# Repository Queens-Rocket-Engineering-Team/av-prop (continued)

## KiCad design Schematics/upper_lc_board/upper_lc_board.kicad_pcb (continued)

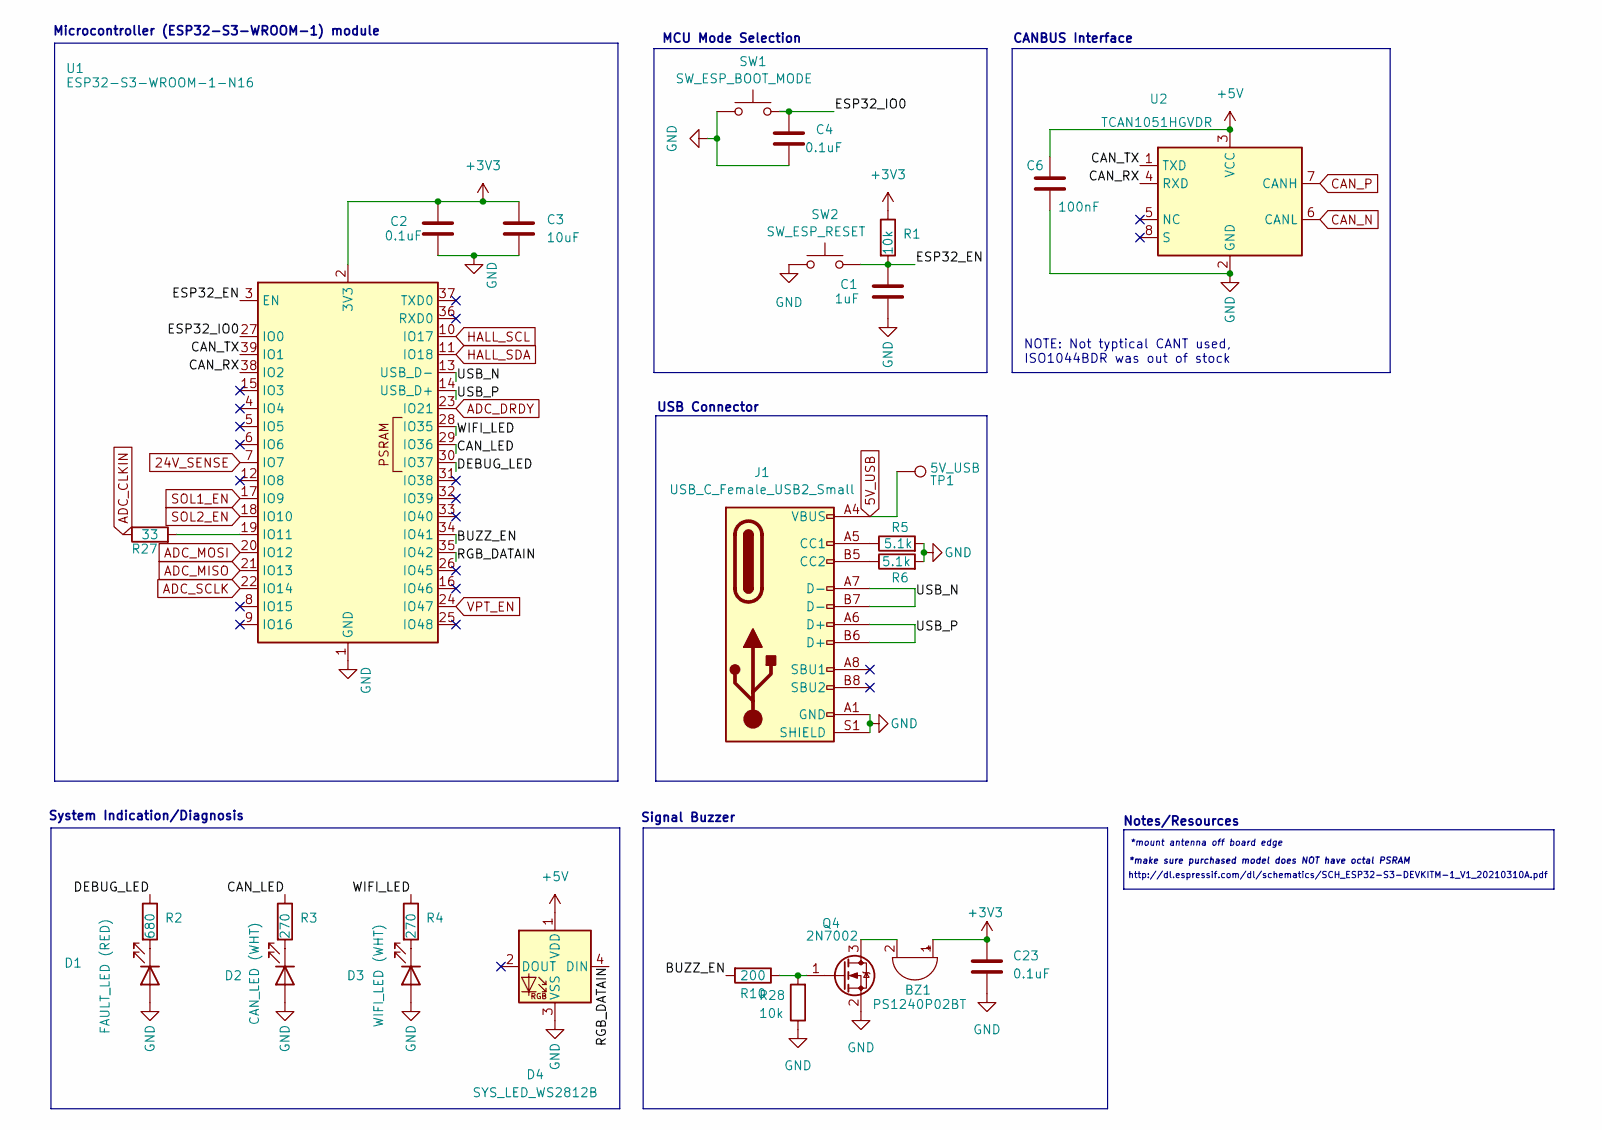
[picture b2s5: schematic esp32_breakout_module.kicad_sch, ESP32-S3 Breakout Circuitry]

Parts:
BZ1: PS1240P02BT; Buzzer_12.6x9.5RM5.0; Digikey 445-2525-1-ND
C1: 1uF; C_0603_1608Metric; LCSC C15849
C2, C4, C23: 0.1uF; C_0603_1608Metric; LCSC C14663
C3: 10uF; C_0603_1608Metric; LCSC C96446
C6: 100nF; C_0603_1608Metric; LCSC C14663
D1: FAULT_LED (RED); LED_0603_1608Metric; LCSC C2286
D2: CAN_LED (WHT); LED_0603_1608Metric; LCSC C2290
D3: WIFI_LED (WHT); LED_0603_1608Metric; LCSC C2290
D4: SYS_LED_WS2812B; LED_WS2812B_PLCC4_5.0x5.0mm_P3.2mm; Digikey 1568-COM-16347CT-ND
J1: USB_C_Female_USB2_Small; USB_C_Receptacle_GCT_USB4105-xx-A_16P_TopMnt_Horizontal; LCSC C5178541
Q4: 2N7002; SOT-23; LCSC C8545
R1, R28: 10k; R_0603_1608Metric; LCSC C25804
R2: 680; R_0603_1608Metric; LCSC C23228
R3, R4: 270; R_0603_1608Metric; LCSC C22966
R5, R6: 5.1k; R_0603_1608Metric; LCSC C23186
R10: 200; R_0603_1608Metric; LCSC C8218
R27: 33; R_0603_1608Metric; LCSC C23140
SW1: SW_ESP_BOOT_MODE; SW_Push_1P1T_XKB_TS-1187A; LCSC C318884
SW2: SW_ESP_RESET; SW_Push_1P1T_XKB_TS-1187A; LCSC C318884
TP1: 5V_USB; TestPoint_Pad_D1.0mm
U1: ESP32-S3-WROOM-1-N16; ESP32-S3-WROOM-1; Digikey 5407-ESP32-S3-WROOM-1-N16CT-ND
U2: TCAN1051HGVDR; SOIC_1044BDR_TEX; Digikey 296-44225-1-ND

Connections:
5V_USB: J1.A4 (VBUS), J1.A9 (VBUS), J1.B4 (VBUS), J1.B9 (VBUS), TP1.1; also elsewhere on the board
24V_SENSE: U1.7 (IO7); also elsewhere on the board
+3V3: BZ1.1 (+), C2.1, C3.1, C23.1, R1.1, U1.2 (3V3); also elsewhere on the board
+5V: C6.2, D4.1 (VDD), U2.3 (VCC); also elsewhere on the board
/ESP32-S3 Breakout Circuitry/BUZZ_IN: R10.2, U1.34 (IO41)
/ESP32-S3 Breakout Circuitry/CAN_LED: R3.1, U1.29 (IO36)
/ESP32-S3 Breakout Circuitry/CAN_RX: U1.38 (IO2), U2.4 (RXD)
/ESP32-S3 Breakout Circuitry/CAN_TX: U1.39 (IO1), U2.1 (TXD)
/ESP32-S3 Breakout Circuitry/DEBUG_LED: R2.1, U1.30 (IO37)
/ESP32-S3 Breakout Circuitry/ESP32_EN: C1.1, R1.2, SW2.2, U1.3 (EN)
/ESP32-S3 Breakout Circuitry/ESP32_IO0: C4.2, SW1.2, U1.27 (IO0)
/ESP32-S3 Breakout Circuitry/RGB_DATAIN: D4.4 (DIN), U1.35 (IO42)
/ESP32-S3 Breakout Circuitry/USB_N: J1.A7 (D-), J1.B7 (D-), U1.13 (USB_D-)
/ESP32-S3 Breakout Circuitry/USB_P: J1.A6 (D+), J1.B6 (D+), U1.14 (USB_D+)
/ESP32-S3 Breakout Circuitry/WIFI_LED: R4.1, U1.28 (IO35)
ADC_CLKIN: R27.1; also elsewhere on the board
ADC_DRDY: U1.23 (IO21); also elsewhere on the board
ADC_MISO: U1.21 (IO13); also elsewhere on the board
ADC_MOSI: U1.20 (IO12); also elsewhere on the board
ADC_SCLK: U1.22 (IO14); also elsewhere on the board
CAN_N: U2.6 (CANL); also elsewhere on the board
CAN_P: U2.7 (CANH); also elsewhere on the board
GND: C1.2, C2.2, C3.2, C4.1, C6.1, C23.2, D1.2 (A), D2.2 (A), D3.2 (A), D4.3 (VSS), J1.A1 (GND), J1.A12 (GND), J1.B1 (GND), J1.B12 (GND), J1.S1 (SHIELD), Q4.2 (S), R5.2, R6.2, R28.1, SW1.1, SW2.1, U1.1 (GND), U1.40 (GND), U1.41 (GND), U2.2 (GND); also elsewhere on the board
HALL_SCL: U1.10 (IO17); also elsewhere on the board
HALL_SDA: U1.11 (IO18); also elsewhere on the board
unnamed: BZ1.2 (-), Q4.3 (D)
unnamed: D1.1 (K), R2.2
unnamed: D2.1 (K), R3.2
unnamed: D3.1 (K), R4.2
unnamed: J1.A5 (CC1), R5.1
unnamed: J1.B5 (CC2), R6.1
unnamed: Q4.1 (G), R10.1, R28.2
unnamed: R27.2, U1.19 (IO11)
SOL1_EN: U1.17 (IO9); also elsewhere on the board
SOL2_EN: U1.18 (IO10); also elsewhere on the board
VPT_EN: U1.24 (IO47); also elsewhere on the board

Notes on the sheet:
CANBUS Interface
Microcontroller (ESP32-S3-WROOM-1) module
*mount antenna off board edge
*make sure purchased model does NOT have octal PSRAM
NOTE: Not typtical CANT used, ISO1044BDR was out of stock
Notes/Resources
MCU Mode Selection
USB Connector
http://dl.espressif.com/dl/schematics/SCH_ESP32-S3-DEVKITM-1_V1_20210310A.pdf
Signal Buzzer
System Indication/Diagnosis

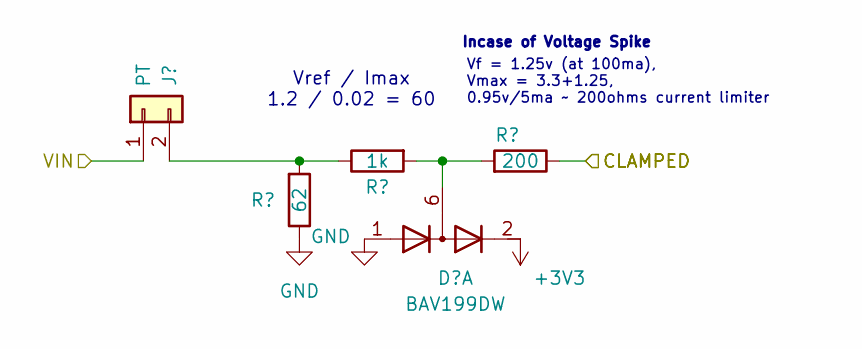
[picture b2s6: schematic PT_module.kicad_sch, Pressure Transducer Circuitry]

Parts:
D11: BAV199DW; SOT-363_SC-70-6; LCSC C459846
J3: PT; MOLEX_1053091102; Digikey WM14965-ND
R11: 62; R_0603_1608Metric; LCSC C23222
R12: 1k; R_0603_1608Metric; LCSC C21190
R13: 200; R_0603_1608Metric; LCSC C8218

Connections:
+3V3: D11.2 (K2), D11.5 (K4); also elsewhere on the board
/Sensing Circuitry/PT1_CLAMPED: R13.1; also elsewhere on the board
GND: D11.1 (A1), D11.4 (A3), R11.1; also elsewhere on the board
unnamed: D11.6 (K3A4), R12.2, R13.2
unnamed 42: D11.3 (K1A2); also elsewhere on the board
unnamed: J3.2, R11.2, R12.1
VPT: J3.1; also elsewhere on the board

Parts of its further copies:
J4: PT; MOLEX_1053091102; Digikey WM14965-ND
R14: 62; R_0603_1608Metric; LCSC C23222
R17: 1k; R_0603_1608Metric; LCSC C21190
R18: 200; R_0603_1608Metric; LCSC C8218

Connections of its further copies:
/Sensing Circuitry/PT2_CLAMPED: R18.1; also elsewhere on the board
GND: R14.1; also elsewhere on the board
unnamed 42: R17.2, R18.2; also elsewhere on the board
unnamed: J4.2, R14.2, R17.1
VPT: J4.1; also elsewhere on the board

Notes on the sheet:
Vf = 1.25v (at 100ma), Vmax = 3.3+1.25, 0.95v/5ma ~ 200ohms current limiter
Incase of Voltage Spike
Vref / Imax 1.2 / 0.02 = 60

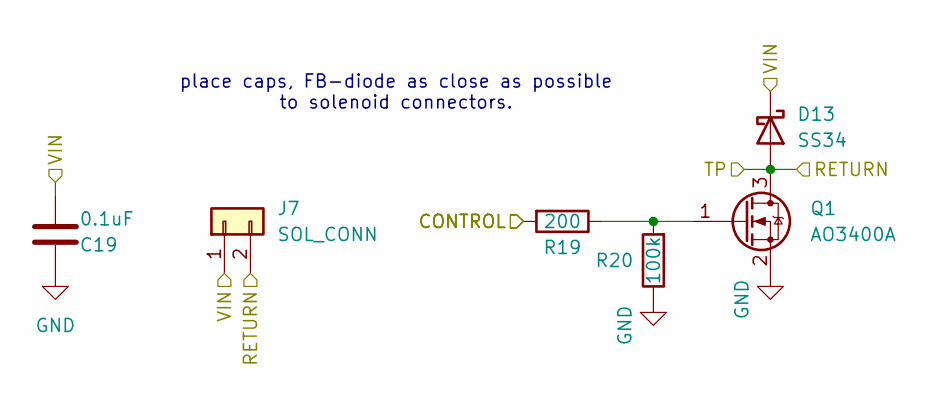
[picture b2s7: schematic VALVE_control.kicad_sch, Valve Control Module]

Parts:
C19: 0.1uF; C_0603_1608Metric; LCSC C14663
D13: SS34; D_SMA; Digikey 5399-SS34CT-ND
J7: SOL_CONN; MOLEX_1053091102; Digikey WM14965-ND
Q1: AO3400A; SOT-23; LCSC C20917
R19: 200; R_0603_1608Metric; LCSC C8218
R20: 100k; R_0603_1608Metric; LCSC C25803

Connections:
+24V: C19.1, D13.1 (K), J7.1; also elsewhere on the board
GND: C19.2, Q1.2 (S), R20.1; also elsewhere on the board
unnamed: Q1.1 (G), R19.1, R20.2
SOL1_EN: R19.2; also elsewhere on the board
SOL1_RET: D13.2 (A), J7.2, Q1.3 (D); also elsewhere on the board

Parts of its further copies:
C21: 0.1uF; C_0603_1608Metric; LCSC C14663
D14: SS34; D_SMA; Digikey 5399-SS34CT-ND
J6: SOL_CONN; MOLEX_1053091102; Digikey WM14965-ND
Q2: AO3400A; SOT-23; LCSC C20917
R26: 200; R_0603_1608Metric; LCSC C8218
R31: 100k; R_0603_1608Metric; LCSC C25803

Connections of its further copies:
+24V: C21.1, D14.1 (K), J6.1; also elsewhere on the board
GND: C21.2, Q2.2 (S), R31.1; also elsewhere on the board
unnamed: Q2.1 (G), R26.1, R31.2
SOL2_EN: R26.2; also elsewhere on the board
SOL2_RET: D14.2 (A), J6.2, Q2.3 (D); also elsewhere on the board

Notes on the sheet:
place caps, FB-diode as close as possible to solenoid connectors.

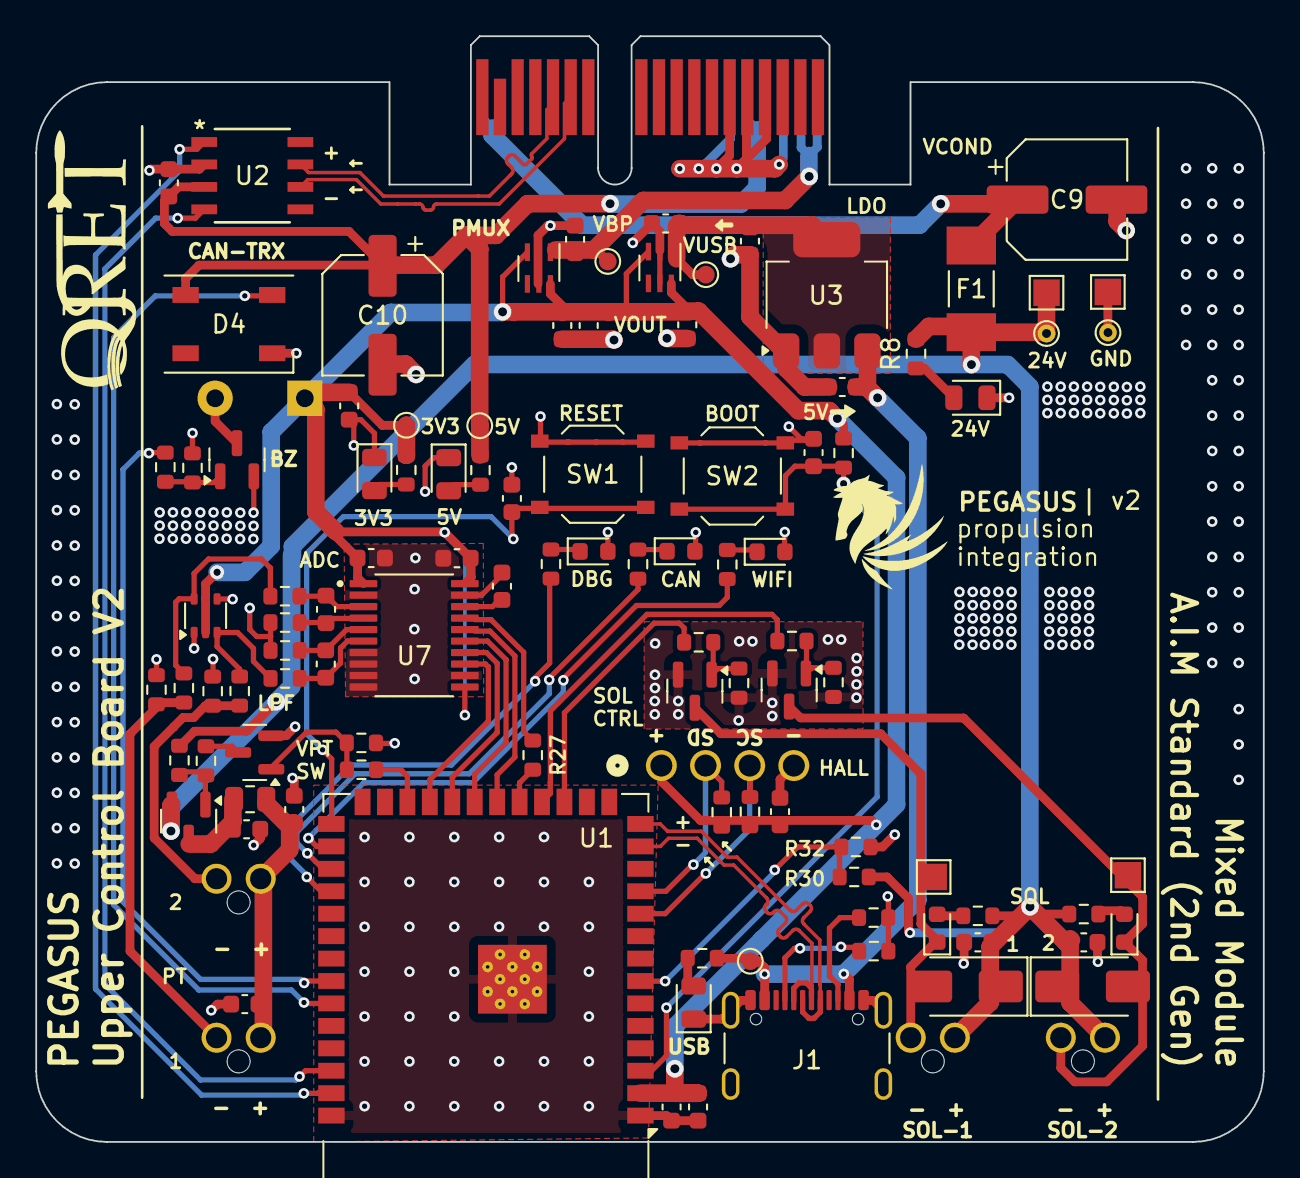
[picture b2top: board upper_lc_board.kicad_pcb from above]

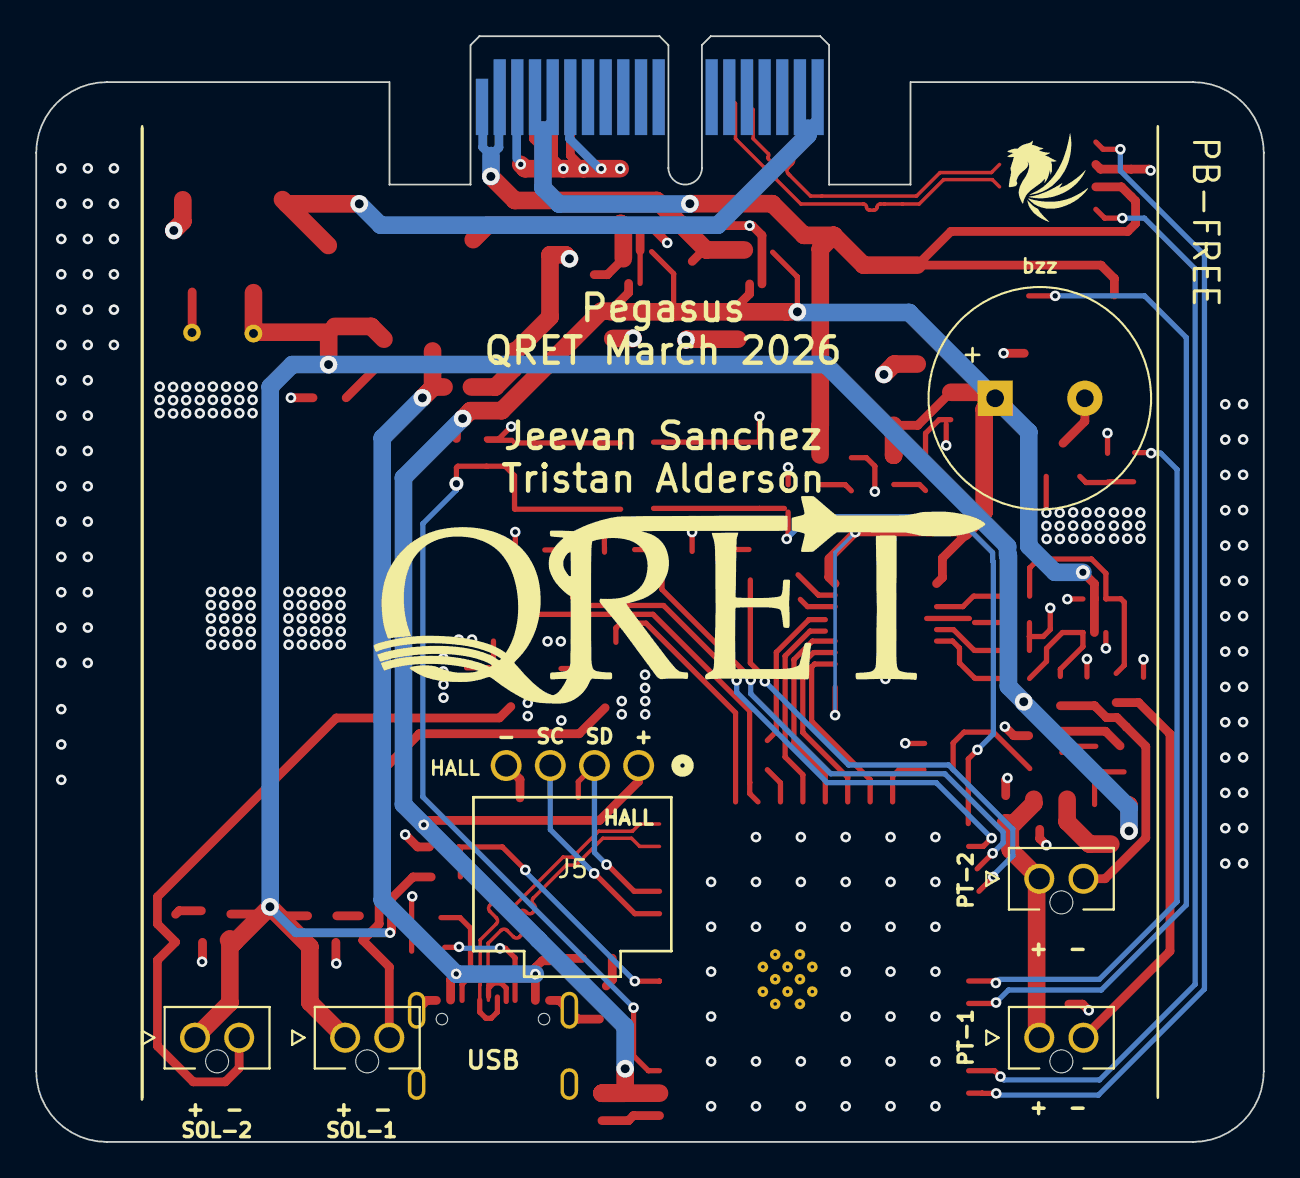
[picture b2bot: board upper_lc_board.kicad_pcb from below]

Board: 4 copper layers, 69.5 x 62.6 mm, 108 parts (6 on the bottom side), 64 nets.

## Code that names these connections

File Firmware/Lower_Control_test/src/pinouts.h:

// Header file containing pinouts for this module 

#ifndef PINOUT_H
#define PINOUT_H

#define FL_CS_PIN PB0
#define VSOL_SENSE_PIN PB1
#define CAN_LED_PIN PB4
#define RGB_DATA_PIN PB5

// I2C-1 BUS
#define HALL_SCL1_PIN PB6
#define HALL_SDA1_PIN PB7

#define CAN_RX_PIN PB8
#define CAN_TX_PIN PB9

// I2C-2 BUS
#define HALL_SCL2_PIN PB10
#define HALL_SDA2_PIN PB11

#define RESET_FL_PIN PB12
#define SOL1_EN_PIN PB13
#define SOL2_EN_PIN PB14

#define ADC_CLKIN_PIN PA0
#define ADC_DRDY_PIN PA1
#define VPT_EN_PIN PA2
#define ADC_CS_PIN PA3
#define CJC_SENSE_PIN PA4 // adc12_in4

// SPI-1 BUS (ADC & FLASH MODULE)
#define SPI_SCLK_PIN PA5
#define SPI_MISO_PIN PA6
#define SPI_MOSI_PIN PA7

#define DB_LED_PIN PA8

// USART-1 (swapped cause of hardware issue)
#define USART_TX_PIN PA9
#define USART_RX_PIN PA10

#define VSOL_EN_PIN PA11

// SW DEBUG
#define SWDIO_PIN PA13
#define SWCLK_PIN PA14

#endif

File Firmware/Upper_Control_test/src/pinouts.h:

// Header file containing pinouts for this module 

#define CAN_TX_PIN 1 
#define CAN_RX_PIN 2 
#define SENSE_24V_PIN 7 
#define SOL1_EN_PIN 9
#define SOL2_EN_PIN 10

// ADC SPI
#define ADC_CLKIN_PIN 11
#define ADC_MOSI_PIN 12
#define ADC_MISO_PIN 13
#define ADC_SCLK_PIN 14

// HALL I2C 
#define HALL_SCL_PIN 17
#define HALL_SDA_PIN 18

#define ADC_DRDY_PIN 19

// iterable
const int WIFI_LED_PIN = 35;
const int CAN_LED_PIN = 36;
const int DEBUG_LED_PIN = 37;

#define BUZZ_EN_PIN 41
#define RGB_DATA_PIN 42
#define VPT_EN_PIN 47

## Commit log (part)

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2026-05-31 add submodules for AimNetwork and qlcp lib, update implementation for AimNetwork 0.4.1
2026-05-31 update gitmodule urls
2026-05-31 Refactor console and node modules to enhance functionality and improve structure
    - Updated platformio.ini to enable MOCK_HARDWARE for testing.
    - Expanded ConsoleMenu in console.cpp to include network, CAN node, and IO control options.
    - Enhanced showMenu function to display new menu options and handle user input for network, CAN, and IO control.
    - Added new console actions in console.h for network, CAN, and IO control.
    - Refactored main.cpp to streamline state transitions and improve watchdog functionality.
    - Updated node.cpp to include additional sensor and valve configurations, and improved telemetry handling.
2026-06-11 Upper_Control: promote config and inline transmit scheduling
    Replace board_config with shared AimNodeConfig, remove AimTxPolicy usage, inline periodic and latched CAN transmit behavior, and clean up local naming conventions.
    Bump av-libraries to the commit containing AimNodeConfig and the TxPolicy removal.
2026-06-11 simplify console, needs matching update from AimFlashStorage/extract_tool
2026-06-11 following changes to console and flash extract tool
2026-06-11 remove artifacts from heave claude use
2026-06-11 av-prop: simplification pass and pin bump (crystalline-exploring-pebble.md)
2026-06-11 av-prop: Upper_Control naming convention cleanup (crystalline-exploring-pebble.md)
2026-06-11 remove references to aim framework in lower fw and update hall library for better dependency injection
2026-06-11 latest stable-v0.5.x cleanup
2026-06-15 av-prop: drop vendored av-libraries submodule, build against workspace copy
    Remove Firmware/av-libraries submodule and its .gitmodules entry; point
    Upper_Control lib_extra_dirs at the workspace ../../../av-libraries/.
2026-06-15 av-prop: add Lower_Control project and refresh Firmware README
2026-06-15 av-prop: migrate Upper_Control to node.* convention
    Replace board.*/console.* with node.{cpp,h} + pinouts.h and a thin
    main.cpp (wiring only). Rename env Upper_Control -> HYDRA, 16MB flash /
    app0 partition layout.
2026-06-16 ucm: clear default WiFi credentials in node.cpp
2026-06-17 minor updates during hardware testing
2026-06-17 fixed: CS pinMode with no pin connected in ADC lib init()
2026-06-18 libraries: add aim_control control model; TMAG5273 getFluxMagnitude
    aim_control is one tagged Control type for actuated outputs on the CAN bus:
    Local controls own a GPIO (de-energized = safe, per-control openLevel) and
    answer Cmd with Ack/State; Remote controls are commanded over CAN with
    seq/retry and tracked via the owner's Ack/State (confirmed only on State).
    TMAG5273 gains getFluxMagnitude() = sqrt(x^2+y^2+z^2), reusing getAllFlux.
2026-06-18 Upper/Lower Control: migrate valves/relays to aim_control
    Replace the hand-rolled valve state + remote CMD/ACK retry queues on both
    boards with a shared aim::Control[] array. Controls and PTs are indexed by
    catalog subject name (kCtrlAv204, kPtPt202, ...) so local vs remote sourcing
    is explicit. UCM shows UNKNOWN for remote controls until the LCM's first
    State confirms them. Pass nowMs into service(); drop CORE_DEBUG_LEVEL spam.
2026-06-21 Upper/Lower Control: aim_sensor + aim_control refactor, fix QLCP sensor_id duplication
    Extract sensor abstraction into aim_sensor library. Simplify aim_control
    polarity model to single defaultOpen bool (removing openLevel). Add
    controlStr() and control name field. Clean up PropTesting constants to
    constexpr kCamelCase. Fix duplicate sensor_id=8 in UCM qlcpTelemetryService
    (now uses UcmSensor enum values). Remove vendored av-libraries submodule.
